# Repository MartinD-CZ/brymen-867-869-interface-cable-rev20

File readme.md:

# Brymen 867/869 adapter cable rev2.0
*see the article [here](http://embedblog.eu/?p=475) or the listing [here](https://www.tindie.com/products/martind/brymen-867869-adapter-cable/)*

## Features
- reads data from Brymen 867/869 via infrared
- sends the measurements at 115200 baud via serial port
- output data rate and format adjustable (5 readings/s, 1 reading/s, single reading); settings are stored in EEPROM and remembered on next power up
- BOOT0 pin available as a button, so you can update the FW without disassembling the case
- activity LED

*Here's how the serial output looks:*

*If you are ordering it without the USB cable, here's how to connect it:*

*Note: previous revisions (1.x) can be found [here](https://github.com/MartinD-CZ/brymen-867-interface-cable/blob/master/README.md)*

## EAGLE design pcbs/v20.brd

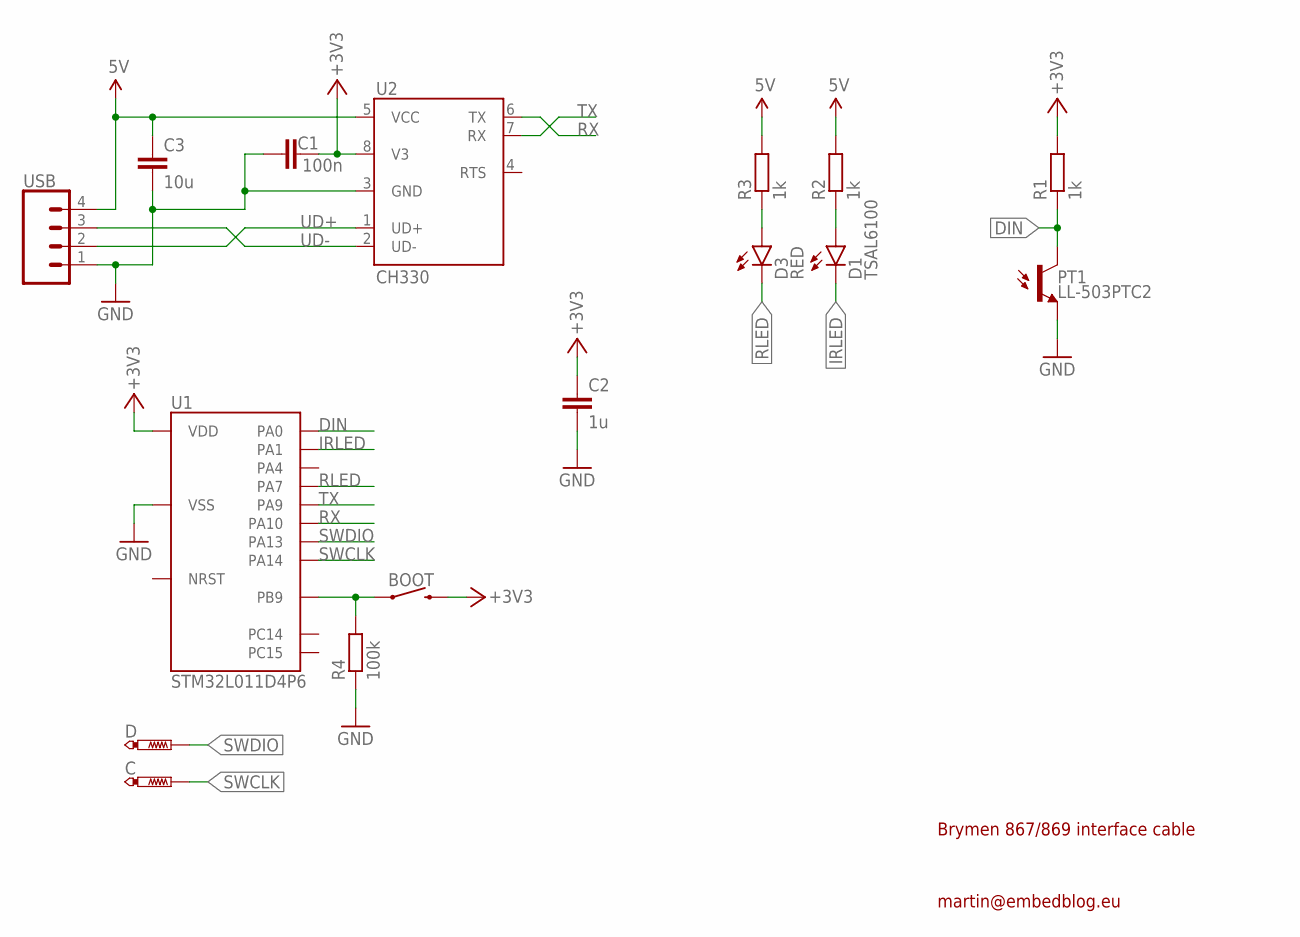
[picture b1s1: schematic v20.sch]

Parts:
BOOT: MOMENTARY-SWITCH-SPST-SMD-5.2MM; TACTILE_SWITCH_SMD_5.2MM
C: PTR1B1,27; B1,27
C1: 100n; C0805
C2: 1u; C0805
C3: 10u; C0805
D: PTR1B1,27; B1,27
D1: TSAL6100; LED5MM
D3: RED; LED-1206
PT1: LL-503PTC2; LED5MM
R1, R2, R3: 1k; R0805
R4: 100k; R0805
U1: STM32L011D4P6; TSSOP14
U2: CH330; SO08
USB: CONN_04; 1X04

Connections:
5V: C3.1, R2.2, R3.2, U2.5 (VCC), USB.4
+3V3: BOOT.3 (2), C1.2, C2.1, R1.2, U1.10 (VDD), U2.8 (V3)
DIN: PT1.K (C), R1.1, U1.5 (PA0)
GND: C1.1, C2.2, C3.2, PT1.A (E), R4.1, U1.9 (VSS), U2.3 (GND), USB.1
IRLED: D1.K (C), U1.6 (PA1)
unnamed: BOOT.1, R4.2, U1.1 (PB9)
unnamed: D1.A, R2.1
unnamed: D3.A, R3.1
RLED: D3.C, U1.8 (PA7)
RX: U1.12 (PA10), U2.6 (TX)
SWCLK: C.TP, U1.14 (PA14)
SWDIO: D.TP, U1.13 (PA13)
TX: U1.11 (PA9), U2.7 (RX)
UD+: U2.1 (UD+), USB.2
UD-: U2.2 (UD-), USB.3

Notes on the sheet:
Brymen 867/869 interface cable
martin@embedblog.eu

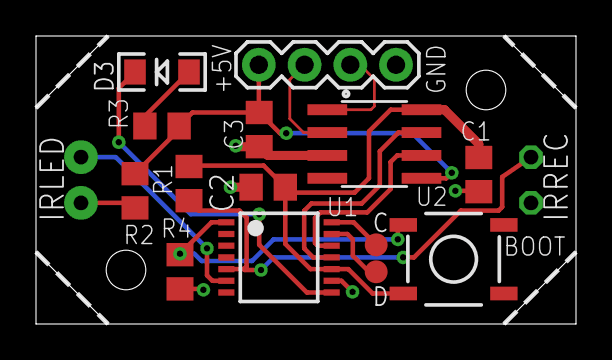
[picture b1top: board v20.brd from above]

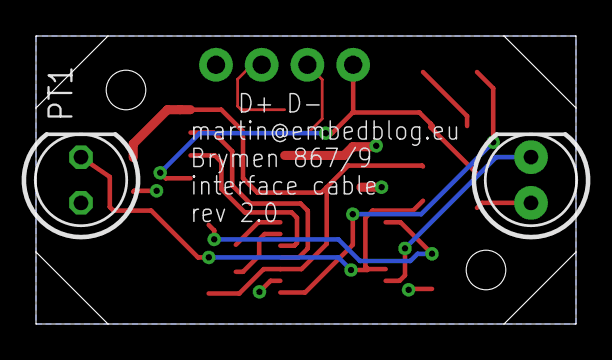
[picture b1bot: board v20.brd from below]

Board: 2 copper layers, 30.0 x 16.0 mm, 16 parts (2 on the bottom side), 15 nets.

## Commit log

2021-04-17 minor fixes
2021-04-17 added automated versioning
2021-04-18 tested EEPROM, added version.h into gitignore
2021-04-19 added decoder & microsend delay
2021-04-25 added basic operation
2021-04-25 added uart command decoding
2021-04-25 added saving to eeprom
2021-04-26 changed gitignore, added startup blink
2021-04-26 changed URL
2021-04-26 reverted gitignore automatic change
2021-04-26 switched off automatic gitgnore modification
2021-04-26 final build
2021-04-26 build tag added
2021-04-28 added readme, case files, pictures
2021-04-28 added PCB files
2021-04-28 disabled optimization on Release configuration
2021-04-29 added console screenshot

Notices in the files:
parts and their libraries:
SparkFun-LED: Licensing: Creative Commons ShareAlike 4.0 International - https://creativecommons.org/licenses/by-sa/4.0
